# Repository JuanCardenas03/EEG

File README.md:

# 🧠⚡ EEG CEGS – Sistema de Captura y Procesamiento de Señales Cerebrales 🧠⚡

> Proyecto desarrollado por estudiantes de Ingeniería Electrónica - UCEVA  
> ¡Captura, procesa y analiza la actividad eléctrica del cerebro con ESP32-S3 y PCB personalizada!

---

## 📋 Descripción del Proyecto

Este proyecto tiene como objetivo el diseño e implementación de un sistema funcional de **electroencefalograma (EEG)**, capaz de capturar y procesar señales cerebrales en tiempo real.

Se ha diseñado una **máquina de estados finita (FSM) tipo Moore**, programada en la **ESP32-S3**, que controla las fases del sistema: desde la captura de señales hasta la presentación del resultado, usando indicadores visuales (LEDs) y entradas táctiles (`Touch 1` y `Touch 2`) para interactuar con el flujo.

---

## 🧩 Características principales

- ✅ Captura de señales EEG por medio de entrada analógica (ADC)
- ✅ Procesamiento interno de señales para detección de transiciones (alfa/beta)
- ✅ Máquina de estados con 4 fases: reposo, captura, procesamiento, resultado
- ✅ Control con sensores táctiles capacitivos (touch)
- ✅ Indicadores LED para mostrar estado del sistema en tiempo real
- ✅ FSM implementada en lenguaje C++ sobre el framework de Arduino
- ✅ PCB diseñada en **Autodesk EAGLE**, lista para fabricación 🛠️📦

---

## 🛠️ Tecnologías y herramientas usadas

- 🔹 ESP32-S3 (WiFi + Touch + ADC + potencia de procesamiento)
- 🔹 EAGLE para diseño de la PCB
- 🔹 Arduino Framework (ESP-IDF también compatible)
- 🔹 Procesamiento básico de señales EEG (FFT futura)
- 🔹 Pantalla OLED para retroalimentación visual
- 🔹 LEDs para retroalimentación visual

---

## 🚀 Estado del proyecto

> En desarrollo activo – se encuentra en fase de pruebas de la FSM y captura de señal.  
> Próximamente se integrará la lógica de procesamiento alfa/beta y se enviará la PCB a fabricación.

---

## 🤝 Aportaciones

¿Tienes experiencia en procesado de señales cerebrales, diseño de filtros, o análisis?  
¡Contribuye con este proyecto abierto! 😄

---

## 📜 Licencia

Este proyecto está bajo licencia **MIT**.  
Puedes usar, modificar y compartir el código libremente, siempre dando crédito a los autores.

---

**Proyecto académico desarrollado por estudiantes de Ingeniería Electrónica – UCEVA**

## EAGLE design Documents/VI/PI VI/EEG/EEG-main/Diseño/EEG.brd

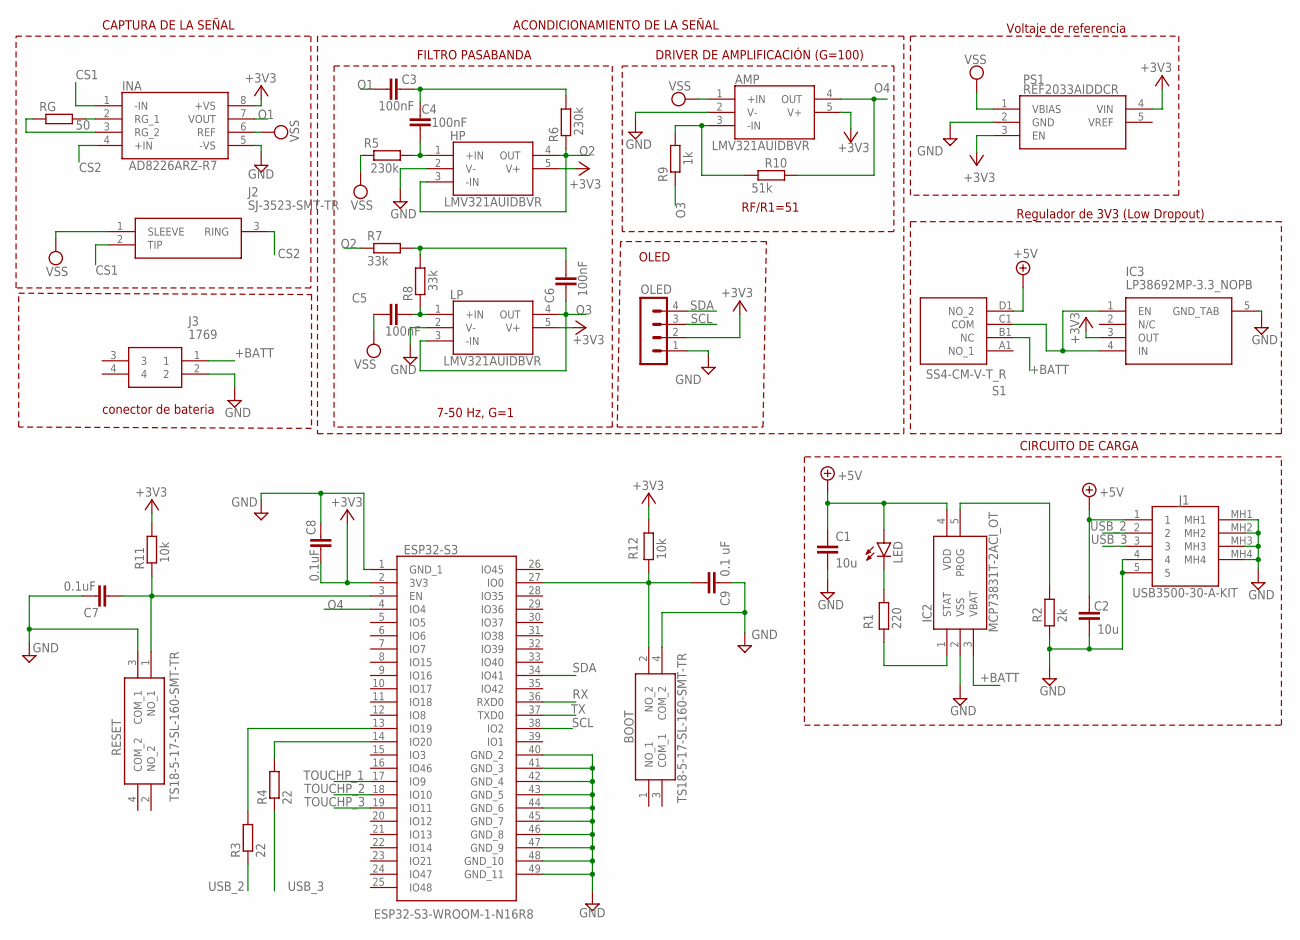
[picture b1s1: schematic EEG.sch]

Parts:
AMP: LMV321AUIDBVR; SOT95P280X145-5N
BOOT: TS18-5-17-SL-160-SMT-TR; TS18517SL160SMTTR
C1, C2: 10u; C0805K
C3, C4, C5, C6: 100nF; C0805
C7, C8: 0.1uF; C0805
C9: 0.1 uF; C0805
ESP32-S3: ESP32-S3-WROOM-1-N16R8; ESP32S3WROOM1N16R8
HP: LMV321AUIDBVR; SOT95P280X145-5N
IC2: MCP73831T-2ACI_OT; SOT95P270X145-5N
IC3: LP38692MP-3.3_NOPB; SOT150P700X180-5N
INA: AD8226ARZ-R7; SOIC127P600X175-8N
J1: USB3500-30-A-KIT; USB350030AKIT
J2: SJ-3523-SMT-TR; SJ3523SMTTR
J3: 1769
LED: LEDCHIPLED_0805; CHIPLED_0805
LP: LMV321AUIDBVR; SOT95P280X145-5N
OLED: MA04-1
PS1: REF2033AIDDCR; SOT95P280X110-5N
R1: 220; R0805
R2: 2k; R0805
R3, R4: 22; R0805
R5, R6: 230k; R0805
R7, R8: 33k; R0805
R9: 1k; R0805
R10: 51k; R0805
R11, R12: 10k; R0805
RESET: TS18-5-17-SL-160-SMT-TR; TS18517SL160SMTTR
RG: 50; M0805
S1: SS4-CM-V-T_R; SS4CMVTR

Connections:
+3V3: AMP.5 (V+), C8.1, ESP32-S3.2 (3V3), HP.5 (V+), IC3.3 (OUT), INA.8 (+VS), LP.5 (V+), OLED.2, PS1.3 (EN), PS1.4 (VIN), R11.2, R12.2
+5V: C1.1, C2.1, IC2.4 (VDD), J1.1, LED.A, S1.D1 (NO_2)
+BATT: IC2.3 (VBAT), J3.1, S1.B1 (NC)
CS1: INA.1 (-IN), J2.2 (TIP)
CS2: INA.4 (+IN), J2.3 (RING)
GND: AMP.2 (V-), BOOT.4 (COM_2), C1.2, C2.2, C7.1, C8.2, C9.1, ESP32-S3.1 (GND_1), ESP32-S3.40 (GND_2), ESP32-S3.41 (GND_3), ESP32-S3.42 (GND_4), ESP32-S3.43 (GND_5), ESP32-S3.44 (GND_6), ESP32-S3.45 (GND_7), ESP32-S3.46 (GND_8), ESP32-S3.47 (GND_9), ESP32-S3.48 (GND_10), ESP32-S3.49 (GND_11), HP.2 (V-), IC2.2 (VSS), IC3.5 (GND_TAB), INA.5 (-VS), J1.4, J1.5, J1.MH1, J1.MH2, J1.MH3, J1.MH4, J3.2, LP.2 (V-), OLED.1, PS1.2 (GND), R2.1, RESET.3 (COM_1)
unnamed: IC2.5 (PROG), R2.2
unnamed: LED.C, R1.2
unnamed: C6.1, R7.2, R8.1
unnamed: C4.2, HP.1 (+IN), R5.2
unnamed: C3.2, C4.1, R6.2
unnamed: C5.1, LP.1 (+IN), R8.2
unnamed: AMP.3 (-IN), R9.2, R10.1
unnamed: INA.2 (RG_1), RG.2
unnamed: IC2.1 (STAT), R1.1
unnamed: IC3.1 (EN), IC3.4 (IN), S1.C1 (COM)
unnamed: INA.3 (RG_2), RG.1
unnamed: BOOT.2 (NO_2), C9.2, ESP32-S3.27 (IO0), R12.1
unnamed: ESP32-S3.14 (IO20), R4.2
unnamed: ESP32-S3.13 (IO19), R3.2
unnamed: C7.2, ESP32-S3.3 (EN), R11.1, RESET.1 (NO_1)
O1: C3.1, INA.7 (VOUT)
O2: HP.3 (-IN), HP.4 (OUT), R6.1, R7.1
O3: C6.2, LP.3 (-IN), LP.4 (OUT), R9.1
O4: AMP.4 (OUT), ESP32-S3.4 (IO4), R10.2
RX: ESP32-S3.36 (RXD0)
SCL: ESP32-S3.38 (IO2), OLED.3
SDA: ESP32-S3.34 (IO41), OLED.4
TOUCHP_1: ESP32-S3.17 (IO9)
TOUCHP_2: ESP32-S3.18 (IO10)
TOUCHP_3: ESP32-S3.19 (IO11)
TX: ESP32-S3.37 (TXD0)
USB_2: J1.2, R3.1
USB_3: J1.3, R4.1
VSS: AMP.1 (+IN), C5.2, INA.6 (REF), J2.1 (SLEEVE), PS1.1 (VBIAS), R5.1

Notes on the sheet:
CAPTURA DE LA SEÑAL
ACONDICIONAMIENTO DE LA SEÑAL
FILTRO PASABANDA
DRIVER DE AMPLIFICACIÓN (G=100)
7-50 Hz, G=1
RF/R1=51
Voltaje de referencia
CIRCUITO DE CARGA
Regulador de 3V3 (Low Dropout)
conector de bateria
OLED

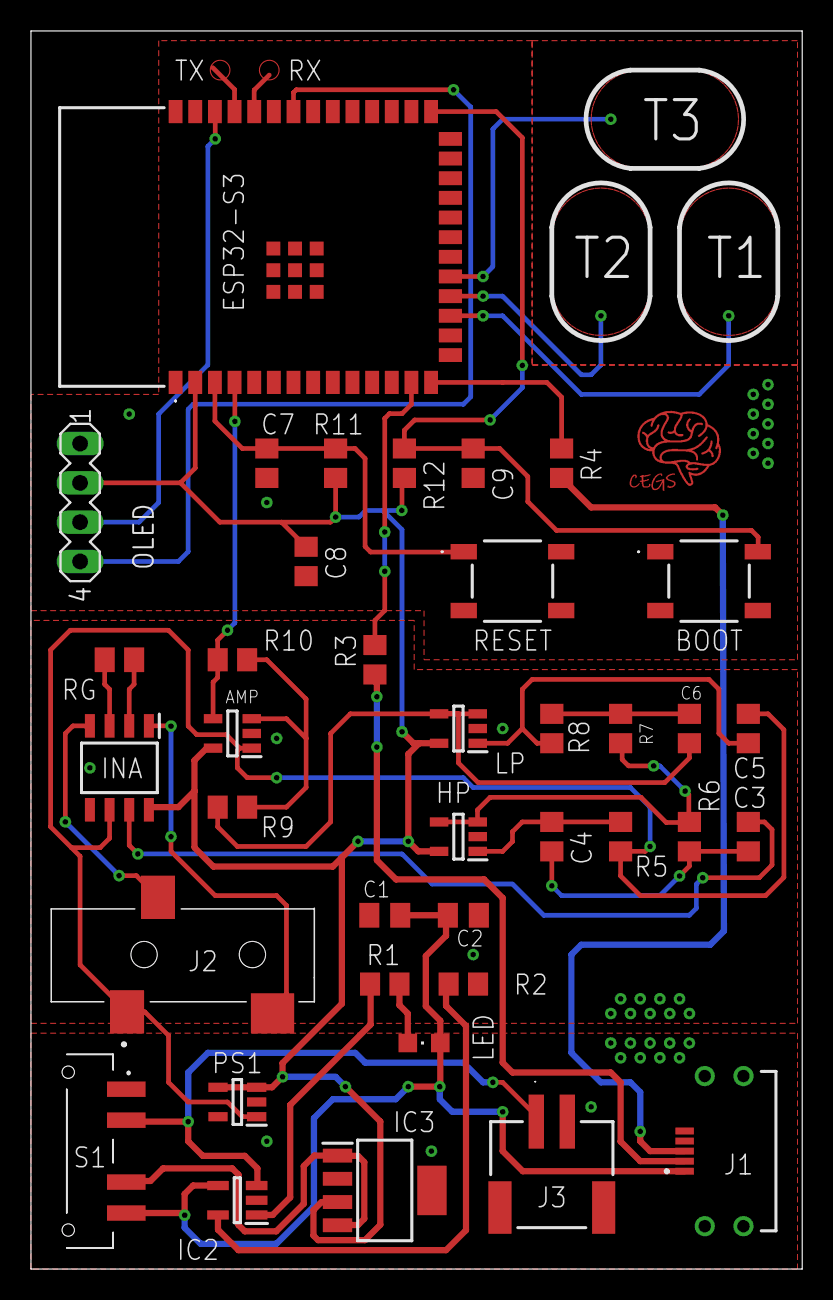
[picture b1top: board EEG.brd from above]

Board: 2 copper layers, 49.8 x 80.0 mm, 38 parts (0 on the bottom side), 30 nets.

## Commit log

2025-03-22 Solo creé el archivo del esquema
2025-03-23 INA medio agregado
2025-03-23 Eliminando archivo innecesario
2025-03-23 Se agregó la forma del filtro pasa banda
2025-03-25 Se añadió la forma del driver amplificador
2025-03-25 Reestructurando el proyecto
2025-03-25 Carpeta del diseño
2025-03-25 Librerías de los componentes
2025-03-25 Se agregó el filtro Notch
2025-03-29 Se reemplazó el INA y se agregó la ESP32 (faltan por configurar)
2025-03-29 Eliminando archivo innecesario (nuevamente)
2025-03-31 se quita el filtro Notch ; a la espera de corregir valores de salidas
2025-03-31 se quita el filtro Notch ; a la espera de corregir valores de salidas v2
2025-03-31 Agregue el voltaje de referecia y conexiones de los amplificadores
2025-03-31 correccion de tierras y entradas 3v3 añadidas (cositas varias)
2025-03-31 correccion de tierras y entradas 3v3 añadidas (cositas varias) v2
2025-04-01 añadido lib de circuito de carga
2025-04-03 Añadido circuito de carga
2025-04-03 Añadido circuito de carga v3
2025-04-03 Añadí el regulador de 3V3 (Low Dropout)
2025-04-03 Se estableció valores de resistores y capacitores para los filtros y amplificadores
2025-04-04 Se subió circuito de la esp32 s3
2025-04-04 Se reorganizó un poco el esquema, se corrigieron algunos errores y se generó el archivo brd
2025-04-04 arreglo de conexiones
2025-04-13 añadido libs para jack y usb, jack añadido falta conexion usb
2025-04-13 correcciones
2025-04-14 Se actualizo el diagrama de la ESP 32-S3
2025-04-14 mod circuito de carga, amplificadores y filtros
2025-04-16 Se actualizó la esp32-s3
2025-04-16 Correcion de conexiones, añadido leds indicadores de estados FSM
2025-04-23 Se cambiaron alguno nombres para evitar confusiones
2025-04-24 Se adelantó la PCB separando los componentes por secciones de potencia, analógica y digital
2025-04-24 añadí el conector de la bateria
2025-04-25 enrutamiento y cambios en la conexion de bateria, Falta GND
2025-04-25 Corrección Esp-32
2025-04-25 añadido paths de resistencias de programación
2025-04-25 correciones de conexion
2025-04-26 arreglé todas las vias de la PCB
2025-04-26 Se agregaron los planos de tierra y se corregieron algunas pistas
2025-04-27 Se agregaron los touchpads
2025-04-29 Se corrigió un par de errores y añadió el logo
2025-05-02 añadido valores cap de carga
2025-05-03 Correcciones del profesor
2025-05-03 añadido oled, componentes nuevos, restio de leds y correcion de pistas
2025-05-03 añadí las rutas del nuevo componente
2025-05-06 por fin acabamos esto
2025-05-28 FSM para esp32
